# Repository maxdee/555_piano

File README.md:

### 555 Piano
inspired by https://circuitdigest.com/electronic-circuits/simple-piano-circuit

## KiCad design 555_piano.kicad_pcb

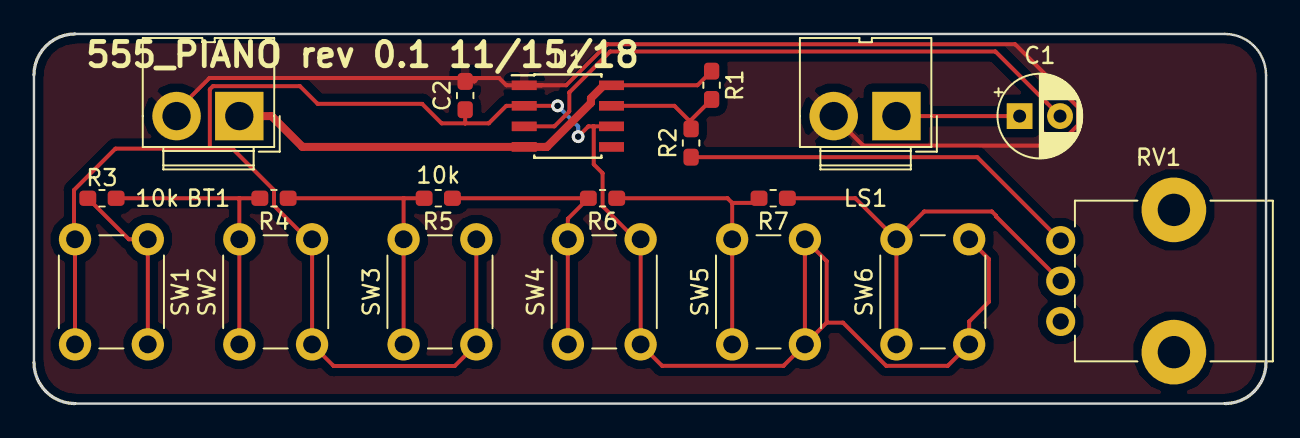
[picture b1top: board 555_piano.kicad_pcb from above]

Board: 2 copper layers, 76.2 x 22.9 mm, 19 parts (0 on the bottom side), 13 nets.

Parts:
BT1: Battery; JWT_A3963_1x02_P3.96mm_Vertical
C1: 10uf; CP_Radial_D5.0mm_P2.50mm
C2: 0.1uf; C_0603_1608Metric_Pad1.05x0.95mm_HandSolder
LS1: Speaker; JWT_A3963_1x02_P3.96mm_Vertical
R1: 2k2; R_0603_1608Metric_Pad1.05x0.95mm_HandSolder
R2: 100; R_0603_1608Metric_Pad1.05x0.95mm_HandSolder
R3, R4, R5, R6, R7: 10k; R_0603_1608Metric_Pad1.05x0.95mm_HandSolder
RV1: R_POT; Potentiometer_Bourns_PTV09A-1_Single_Vertical
SW1, SW2, SW3, SW5, SW6: SW_Push; SW_PUSH_6mm_H7.3mm
SW4: E#; SW_PUSH_6mm_H7.3mm
U1: NE555; SOIC-8_3.9x4.9mm_P1.27mm

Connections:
/SPEAKER: C1.2, U1.3
GND: BT1.2, C2.2, LS1.2, U1.1
unnamed: C1.1, LS1.1
unnamed: C2.1, SW1.2, SW2.2, SW3.2, SW4.2, SW5.2, SW6.2, U1.2, U1.6
unnamed: R1.2, R2.2, U1.7
unnamed: R2.1, RV1.3
unnamed: R3.1, R4.2, SW2.1
unnamed: R3.2, SW1.1
unnamed: R4.1, R5.2, SW3.1
unnamed: R5.1, R6.2, SW4.1
unnamed: R6.1, R7.2, SW5.1
unnamed: R7.1, RV1.2, SW6.1
VCC: BT1.1, R1.1, U1.4, U1.8
